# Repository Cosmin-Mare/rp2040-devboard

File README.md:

# RP2040 Dev Board

A small, Pico-style development board built around the **RP2040**, designed in **KiCad 10**. USB-C, 3.3 V LDO, 2 MB QSPI flash, a BOOTSEL button, SWD header, and every GPIO broken out to two 20-pin 2.54 mm headers. 

|          |                                                                            |
| -------- | -------------------------------------------------------------------------- |
| MCU      | Raspberry Pi RP2040 (QFN-56), 12 MHz crystal                               |
| Flash    | Winbond W25Q16JV, 16 Mbit (2 MB) QSPI                                      |
| Power    | USB-C (5 V) → MCP1700-3.3 LDO (250 mA)                                     |
| I/O      | 26 GPIO (incl. 4 ADC), RUN, VBUS, 3V3, GND on headers; 3-pin SWD (1.27 mm) |
| Controls | BOOTSEL button (no reset button – RUN is on a header pin)                  |
| Board    | 21 × 51 mm, 2-layer, 1.6 mm, headers 17.78 mm (700 mil) apart              |
| Assembly | All SMD on the top side (JLCPCB), pin headers hand-soldered                |

## Repository layout

```
hardware/kicad/        KiCad 10 project (schematic + PCB) – the source of truth
fabrication/gerbers/   Gerbers, drill files, .gbrjob exported from KiCad
fabrication/jlcpcb/    Ready-to-upload files: gerbers zip, bom.csv, cpl.csv
fabrication/extras/    IPC-D-356 netlist, ODB++, IPC-2581 XML, KiCad board report (.rpt)
bom/bom.csv            Full BOM with MPN + LCSC numbers
bom/BOM.md             Readable BOM
bom/jlcpcb-bom-match-*.xlsx   JLCPCB's BOM-tool match result (stock/prices at the time)
docs/ORDERING.md       Step-by-step JLCPCB order
docs/ASSEMBLY.md       What JLCPCB places vs. what you solder, plus hand-assembly notes
docs/BRINGUP.md       First power-up, flashing, and test checklist
docs/PINOUT.md         Header pinout
```

## Quick start

1. **Order** – follow [docs/ORDERING.md](docs/ORDERING.md). Upload `fabrication/jlcpcb/devboard-gerbers.zip`, then `bom.csv` and `cpl.csv`.
2. **Solder** the two 20-pin headers (and optionally the SWD header) – see [docs/ASSEMBLY.md](docs/ASSEMBLY.md).
3. **Bring up** – hold BOOTSEL, plug in USB-C, copy a `.uf2` onto the `RPI-RP2` drive. See [docs/BRINGUP.md](docs/BRINGUP.md).

## Editing the design

Open `hardware/kicad/devboard.kicad_pro` in KiCad 10. After changes, re-export Gerbers/drill (`File → Fabrication Outputs`), and the position file (`Fabrication Outputs → Component Placement`, CSV, SMD only, millimetres), then refresh `fabrication/` and `bom/`.

## Bill of Materials

Per board. 33 parts total (16 line items). Full data incl. manufacturer/MPN in [bom.csv](bom.csv).

| Designators | Qty | Value | Footprint | MPN | LCSC | Assembled by JLCPCB |
|---|--:|---|---|---|---|---|
| C1,C10 | 2 | 1uF | C_0402_1005Metric | CL05A105KA5NQNC | [C52923](https://www.lcsc.com/product-detail/C52923.html) | Yes |
| C2,C3,C4,C5,C6,C7,C8,C9,C11,C12,C17 | 11 | 0.1uF | C_0402_1005Metric | CL05B104KO5NNNC | [C1525](https://www.lcsc.com/product-detail/C1525.html) | Yes |
| C13,C14 | 2 | 10uF | C_0603_1608Metric | CL10A106KP8NNNC | [C19702](https://www.lcsc.com/product-detail/C19702.html) | Yes |
| C15,C16 | 2 | 33pF | C_0402_1005Metric | 0402CG330J500NT | [C1562](https://www.lcsc.com/product-detail/C1562.html) | Yes |
| J1 | 1 | USB_C_Receptacle_USB2.0_14P | USB_C_Receptacle_HRO_TYPE-C-31-M-12 | TYPE-C-31-M-12 | [C165948](https://www.lcsc.com/product-detail/C165948.html) | Yes |
| J2,J3 | 2 | Conn_01x20 | PinHeader_1x20_P2.54mm_Vertical | 2.54-1*20P直针 | [C50981](https://www.lcsc.com/product-detail/C50981.html) | No (hand-solder) |
| J4 | 1 | Conn_01x03 | PinHeader_1x03_P2.54mm_Vertical | 1.27-1*3P针 | [C24980](https://www.lcsc.com/product-detail/C24980.html) | No (hand-solder) |
| R1,R2 | 2 | 5.1k | R_0402_1005Metric | 0402WGF5101TCE | [C25905](https://www.lcsc.com/product-detail/C25905.html) | Yes |
| R3,R4 | 2 | 27 | R_0402_1005Metric | 0402WGF270JTCE | [C25100](https://www.lcsc.com/product-detail/C25100.html) | Yes |
| R5,R7 | 2 | 1k | R_0402_1005Metric | 0402WGF1001TCE | [C11702](https://www.lcsc.com/product-detail/C11702.html) | Yes |
| R6 | 1 | 10k | R_0402_1005Metric | 0402WGF1002TCE | [C25744](https://www.lcsc.com/product-detail/C25744.html) | Yes |
| SW1 | 1 | SW_Push | SW_Push_SPST_NO_Alps_SKRK | TS-1088-AR02016 | [C720477](https://www.lcsc.com/product-detail/C720477.html) | Yes |
| U1 | 1 | RP2040 | QFN-56-1EP_7x7mm_P0.4mm_EP3.2x3.2mm | RP2040 | [C2040](https://www.lcsc.com/product-detail/C2040.html) | Yes |
| U2 | 1 | MCP1700x-330xxTT | SOT-23 | MCP1700T-3302E/TT | [C39051](https://www.lcsc.com/product-detail/C39051.html) | Yes |
| U3 | 1 | W25Q16JVZPIQTR | Winbond_USON-8-1EP_3x2mm_P0.5mm_EP0.2x1.6mm | W25Q16JVUXIQ | [C2843335](https://www.lcsc.com/product-detail/C2843335.html) | Yes |
| Y1 | 1 | 12MHz | Crystal_SMD_3225-4Pin_3.2x2.5mm | X322512MSB4SI | [C9002](https://www.lcsc.com/product-detail/C9002.html) | Yes |

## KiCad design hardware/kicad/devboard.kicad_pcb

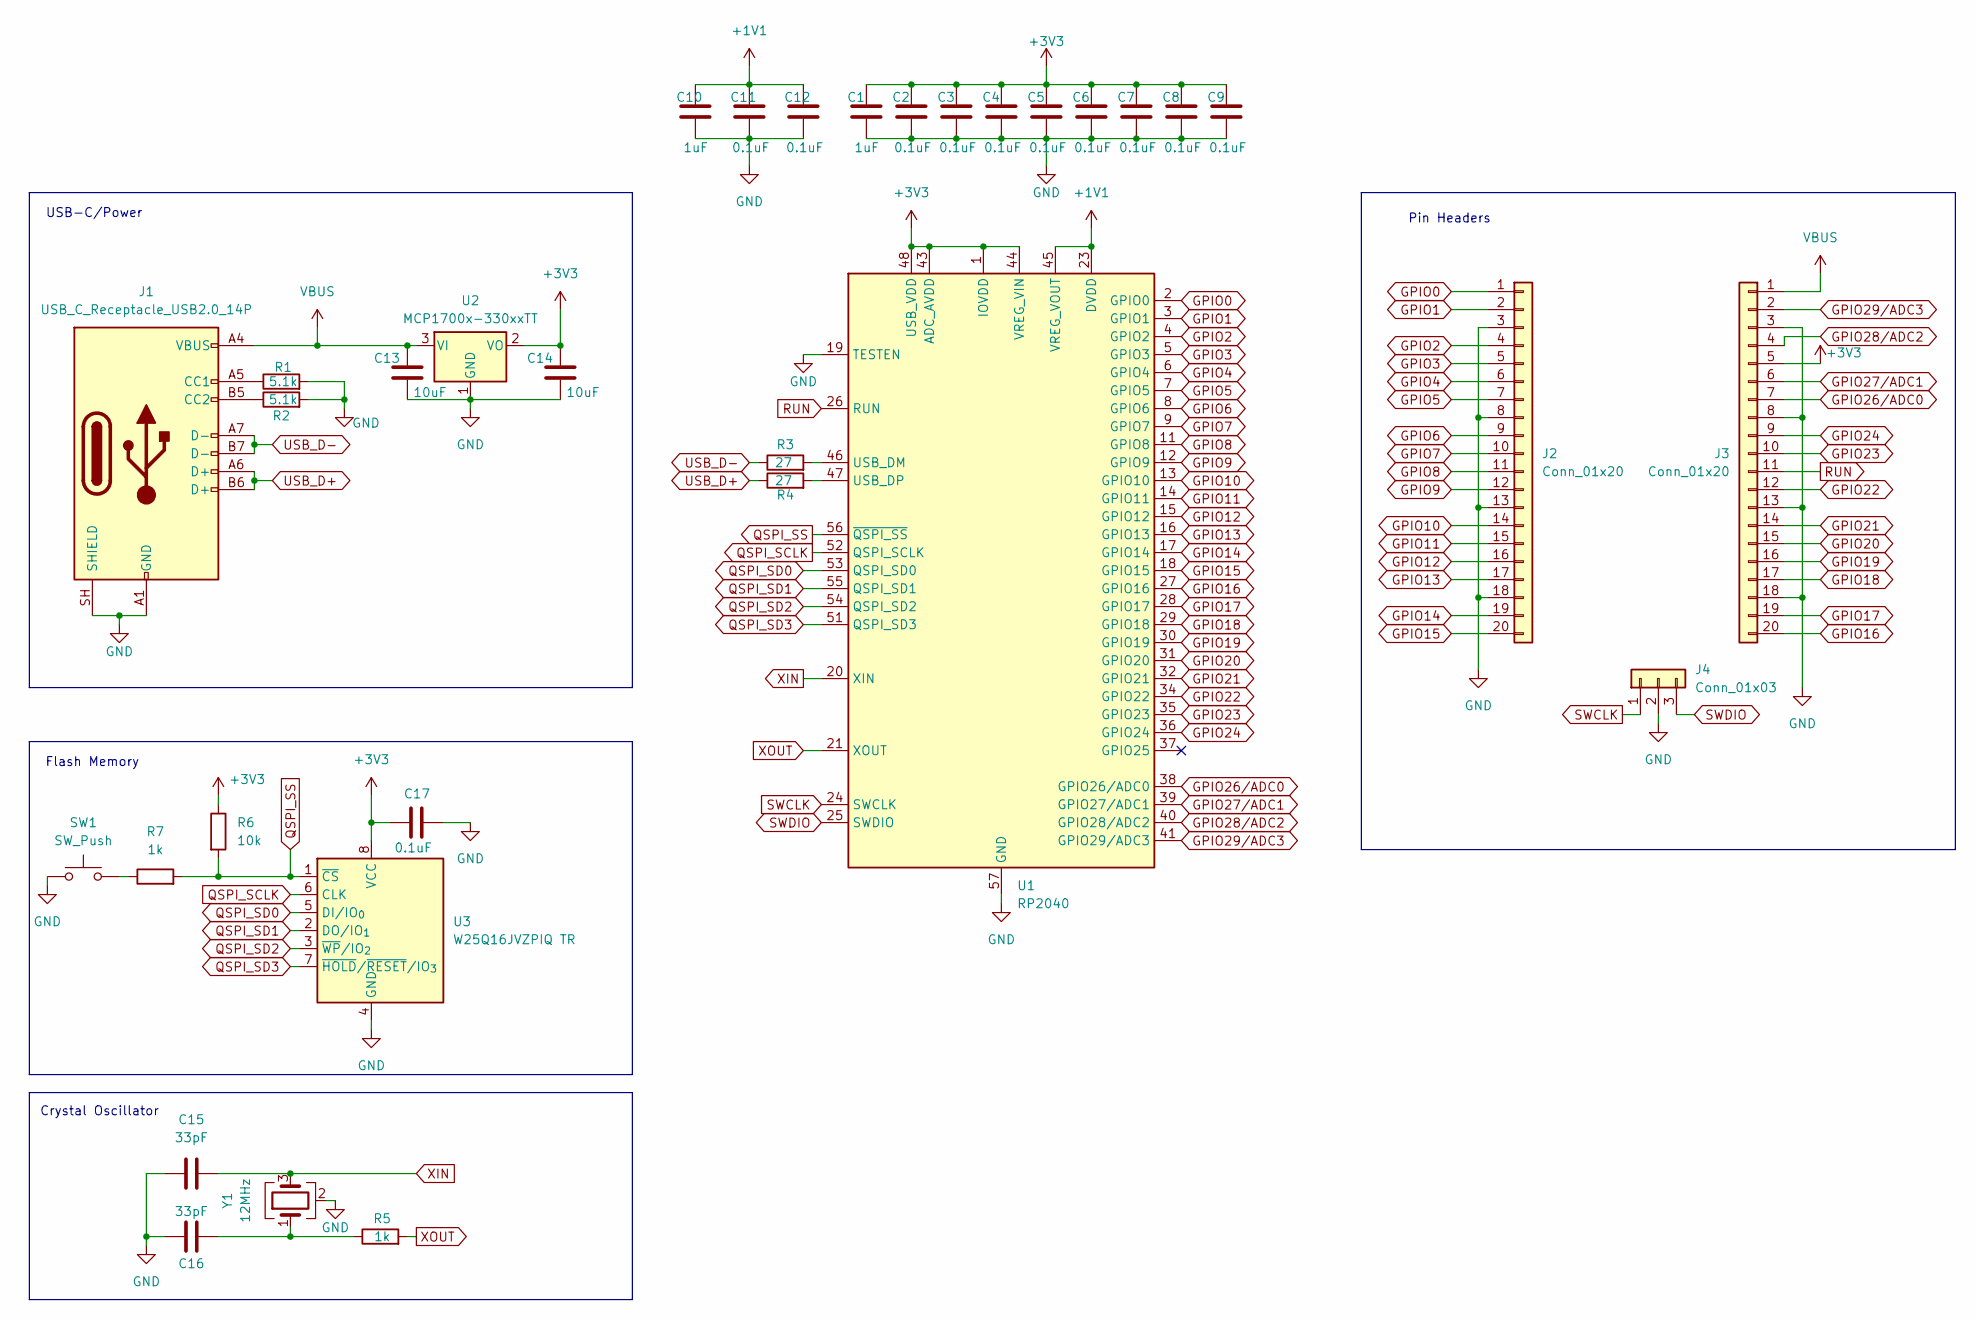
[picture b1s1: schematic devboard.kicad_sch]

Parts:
C1, C10: 1uF; C_0402_1005Metric
C2, C3, C4, C5, C6, C7, C8, C9, C11, C12, C17: 0.1uF; C_0402_1005Metric
C13, C14: 10uF; C_0603_1608Metric
C15, C16: 33pF; C_0402_1005Metric
J1: USB_C_Receptacle_USB2.0_14P; USB_C_Receptacle_HRO_TYPE-C-31-M-12
J2, J3: Conn_01x20; PinHeader_1x20_P2.54mm_Vertical
J4: Conn_01x03; PinHeader_1x03_P2.54mm_Vertical
R1, R2: 5.1k; R_0402_1005Metric
R3, R4: 27; R_0402_1005Metric
R5, R7: 1k; R_0402_1005Metric
R6: 10k; R_0402_1005Metric
SW1: SW_Push; SW_Push_SPST_NO_Alps_SKRK
U1: RP2040; QFN-56-1EP_7x7mm_P0.4mm_EP3.2x3.2mm
U2: MCP1700x-330xxTT; SOT-23
U3: W25Q16JVZPIQ TR; Winbond_USON-8-1EP_3x2mm_P0.5mm_EP0.2x1.6mm
Y1: 12MHz; Crystal_SMD_3225-4Pin_3.2x2.5mm

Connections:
+1V1: C10.1, C11.1, C12.1, U1.23 (DVDD), U1.45 (VREG_VOUT), U1.50 (DVDD)
+3V3: C1.1, C2.1, C3.1, C4.1, C5.1, C6.1, C7.1, C8.1, C9.1, C14.1, C17.1, J3.5, R6.1, U1.1 (IOVDD), U1.10 (IOVDD), U1.22 (IOVDD), U1.33 (IOVDD), U1.42 (IOVDD), U1.43 (ADC_AVDD), U1.44 (VREG_VIN), U1.48 (USB_VDD), U1.49 (IOVDD), U2.2 (VO), U3.8 (VCC)
GND: C1.2, C2.2, C3.2, C4.2, C5.2, C6.2, C7.2, C8.2, C9.2, C10.2, C11.2, C12.2, C13.2, C14.2, C15.1, C16.1, C17.2, J1.A1 (GND), J1.A12 (GND), J1.B1 (GND), J1.B12 (GND), J1.SH (SHIELD), J2.3, J2.8, J2.13, J2.18, J3.3, J3.8, J3.13, J3.18, J4.2, R1.2, R2.2, SW1.1, U1.19 (TESTEN), U1.57 (GND), U2.1 (GND), U3.4 (GND), Y1.2 (G), Y1.4 (G)
GPIO0: J2.1, U1.2 (GPIO0)
GPIO1: J2.2, U1.3 (GPIO1)
GPIO2: J2.4, U1.4 (GPIO2)
GPIO3: J2.5, U1.5 (GPIO3)
GPIO4: J2.6, U1.6 (GPIO4)
GPIO5: J2.7, U1.7 (GPIO5)
GPIO6: J2.9, U1.8 (GPIO6)
GPIO7: J2.10, U1.9 (GPIO7)
GPIO8: J2.11, U1.11 (GPIO8)
GPIO9: J2.12, U1.12 (GPIO9)
GPIO10: J2.14, U1.13 (GPIO10)
GPIO11: J2.15, U1.14 (GPIO11)
GPIO12: J2.16, U1.15 (GPIO12)
GPIO13: J2.17, U1.16 (GPIO13)
GPIO14: J2.19, U1.17 (GPIO14)
GPIO15: J2.20, U1.18 (GPIO15)
GPIO16: J3.20, U1.27 (GPIO16)
GPIO17: J3.19, U1.28 (GPIO17)
GPIO18: J3.17, U1.29 (GPIO18)
GPIO19: J3.16, U1.30 (GPIO19)
GPIO20: J3.15, U1.31 (GPIO20)
GPIO21: J3.14, U1.32 (GPIO21)
GPIO22: J3.12, U1.34 (GPIO22)
GPIO23: J3.10, U1.35 (GPIO23)
GPIO24: J3.9, U1.36 (GPIO24)
GPIO26/ADC0: J3.7, U1.38 (GPIO26/ADC0)
GPIO27/ADC1: J3.6, U1.39 (GPIO27/ADC1)
GPIO28/ADC2: J3.4, U1.40 (GPIO28/ADC2)
GPIO29/ADC3: J3.2, U1.41 (GPIO29/ADC3)
unnamed: C16.2, R5.1, Y1.1
unnamed: J1.A5 (CC1), R1.1
unnamed: J1.B5 (CC2), R2.1
unnamed: R7.1, SW1.2
unnamed: R3.2, U1.46 (USB_DM)
unnamed: R4.2, U1.47 (USB_DP)
QSPI_SCLK: U1.52 (QSPI_SCLK), U3.6 (CLK)
QSPI_SD0: U1.53 (QSPI_SD0), U3.5 (DI/IO_{0})
QSPI_SD1: U1.55 (QSPI_SD1), U3.2 (DO/IO_{1})
QSPI_SD2: U1.54 (QSPI_SD2), U3.3 (~WP/IO_{2})
QSPI_SD3: U1.51 (QSPI_SD3), U3.7 (~HOLD/~RESET/IO_{3})
QSPI_SS: R6.2, R7.2, U1.56 (~QSPI_SS), U3.1 (~CS)
RUN: J3.11, U1.26 (RUN)
SWCLK: J4.1, U1.24 (SWCLK)
SWDIO: J4.3, U1.25 (SWDIO)
USB_D+: J1.A6 (D+), J1.B6 (D+), R4.1
USB_D-: J1.A7 (D-), J1.B7 (D-), R3.1
VBUS: C13.1, J1.A4 (VBUS), J1.A9 (VBUS), J1.B4 (VBUS), J1.B9 (VBUS), J3.1, U2.3 (VI)
XIN: C15.2, U1.20 (XIN), Y1.3
XOUT: R5.2, U1.21 (XOUT)

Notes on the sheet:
USB-C/Power
Crystal Oscillator
Pin Headers
Flash Memory

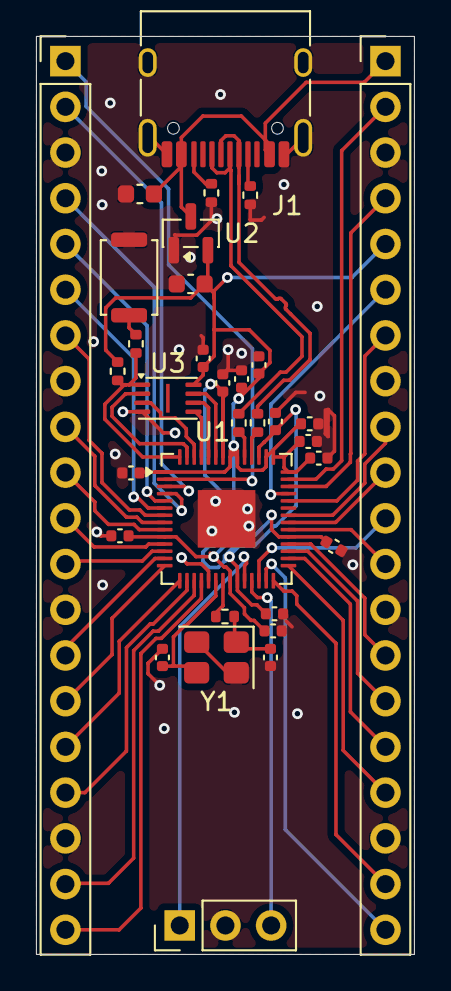
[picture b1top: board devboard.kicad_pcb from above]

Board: 2 copper layers, 21.0 x 51.0 mm, 33 parts (0 on the bottom side), 52 nets.

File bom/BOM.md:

# Bill of Materials

Per board. 33 parts total (16 line items). Full data incl. manufacturer/MPN in [bom.csv](bom.csv).

| Designators | Qty | Value | Footprint | MPN | LCSC | Assembled by JLCPCB |
|---|--:|---|---|---|---|---|
| C1,C10 | 2 | 1uF | C_0402_1005Metric | CL05A105KA5NQNC | [C52923](https://www.lcsc.com/product-detail/C52923.html) | Yes |
| C2,C3,C4,C5,C6,C7,C8,C9,C11,C12,C17 | 11 | 0.1uF | C_0402_1005Metric | CL05B104KO5NNNC | [C1525](https://www.lcsc.com/product-detail/C1525.html) | Yes |
| C13,C14 | 2 | 10uF | C_0603_1608Metric | CL10A106KP8NNNC | [C19702](https://www.lcsc.com/product-detail/C19702.html) | Yes |
| C15,C16 | 2 | 33pF | C_0402_1005Metric | 0402CG330J500NT | [C1562](https://www.lcsc.com/product-detail/C1562.html) | Yes |
| J1 | 1 | USB_C_Receptacle_USB2.0_14P | USB_C_Receptacle_HRO_TYPE-C-31-M-12 | TYPE-C-31-M-12 | [C165948](https://www.lcsc.com/product-detail/C165948.html) | Yes |
| J2,J3 | 2 | Conn_01x20 | PinHeader_1x20_P2.54mm_Vertical | 2.54-1*20P直针 | [C50981](https://www.lcsc.com/product-detail/C50981.html) | No (hand-solder) |
| J4 | 1 | Conn_01x03 | PinHeader_1x03_P2.54mm_Vertical | 1.27-1*3P针 | [C24980](https://www.lcsc.com/product-detail/C24980.html) | No (hand-solder) |
| R1,R2 | 2 | 5.1k | R_0402_1005Metric | 0402WGF5101TCE | [C25905](https://www.lcsc.com/product-detail/C25905.html) | Yes |
| R3,R4 | 2 | 27 | R_0402_1005Metric | 0402WGF270JTCE | [C25100](https://www.lcsc.com/product-detail/C25100.html) | Yes |
| R5,R7 | 2 | 1k | R_0402_1005Metric | 0402WGF1001TCE | [C11702](https://www.lcsc.com/product-detail/C11702.html) | Yes |
| R6 | 1 | 10k | R_0402_1005Metric | 0402WGF1002TCE | [C25744](https://www.lcsc.com/product-detail/C25744.html) | Yes |
| SW1 | 1 | SW_Push | SW_Push_SPST_NO_Alps_SKRK | TS-1088-AR02016 | [C720477](https://www.lcsc.com/product-detail/C720477.html) | Yes |
| U1 | 1 | RP2040 | QFN-56-1EP_7x7mm_P0.4mm_EP3.2x3.2mm | RP2040 | [C2040](https://www.lcsc.com/product-detail/C2040.html) | Yes |
| U2 | 1 | MCP1700x-330xxTT | SOT-23 | MCP1700T-3302E/TT | [C39051](https://www.lcsc.com/product-detail/C39051.html) | Yes |
| U3 | 1 | W25Q16JVZPIQTR | Winbond_USON-8-1EP_3x2mm_P0.5mm_EP0.2x1.6mm | W25Q16JVUXIQ | [C2843335](https://www.lcsc.com/product-detail/C2843335.html) | Yes |
| Y1 | 1 | 12MHz | Crystal_SMD_3225-4Pin_3.2x2.5mm | X322512MSB4SI | [C9002](https://www.lcsc.com/product-detail/C9002.html) | Yes |
